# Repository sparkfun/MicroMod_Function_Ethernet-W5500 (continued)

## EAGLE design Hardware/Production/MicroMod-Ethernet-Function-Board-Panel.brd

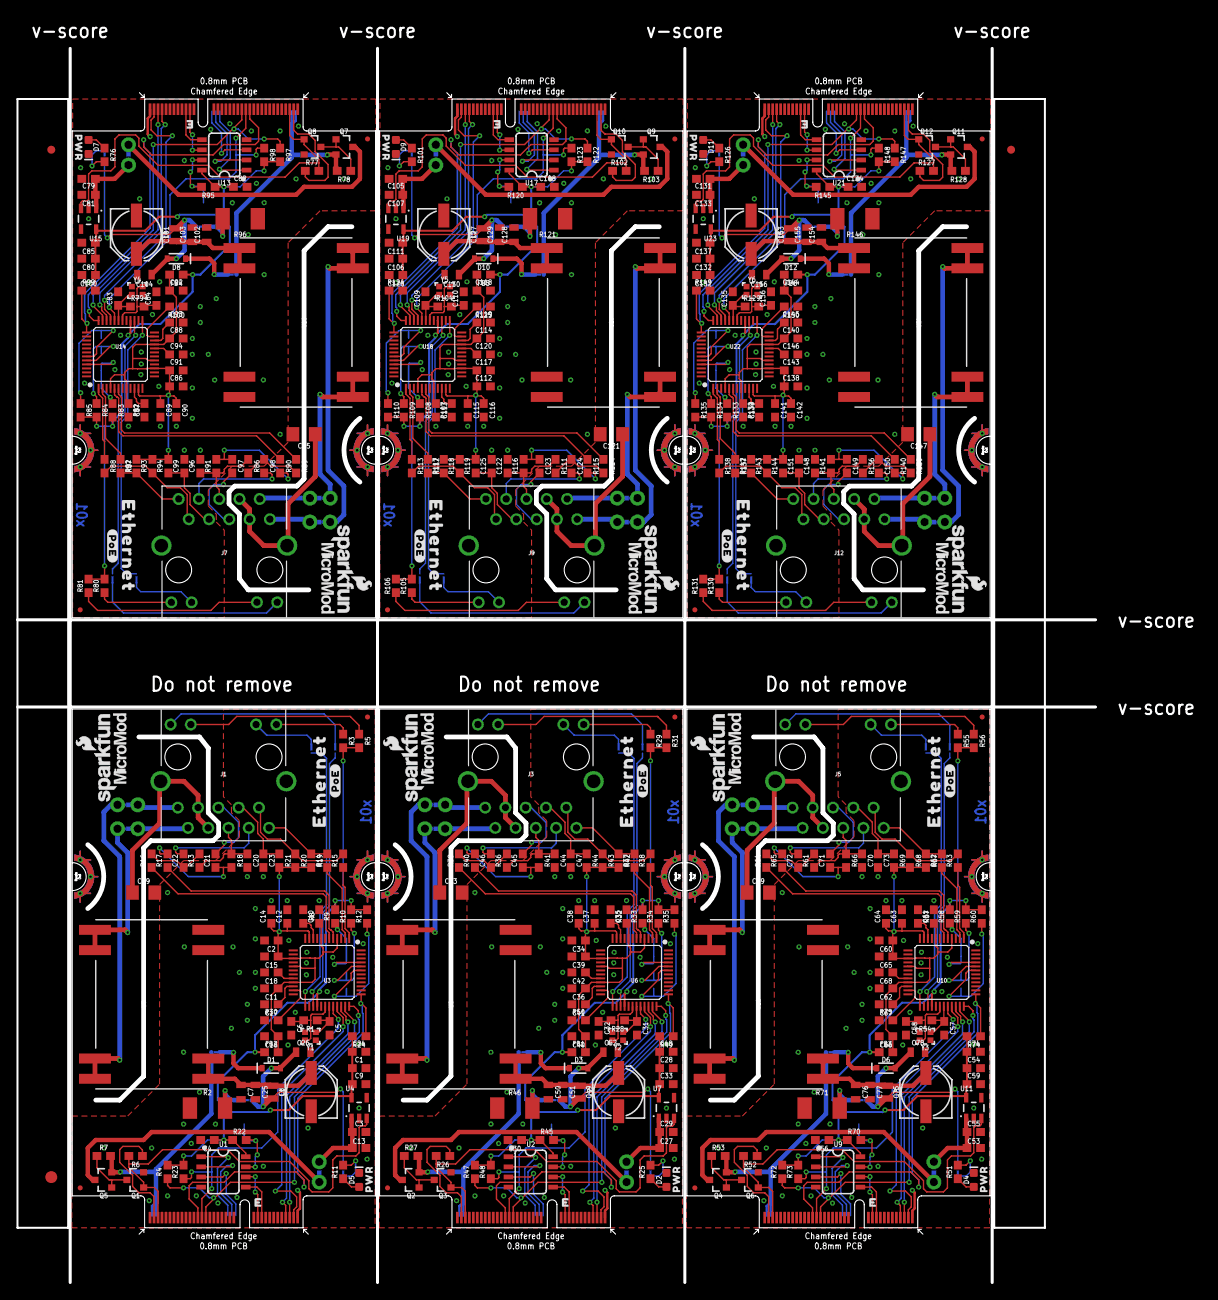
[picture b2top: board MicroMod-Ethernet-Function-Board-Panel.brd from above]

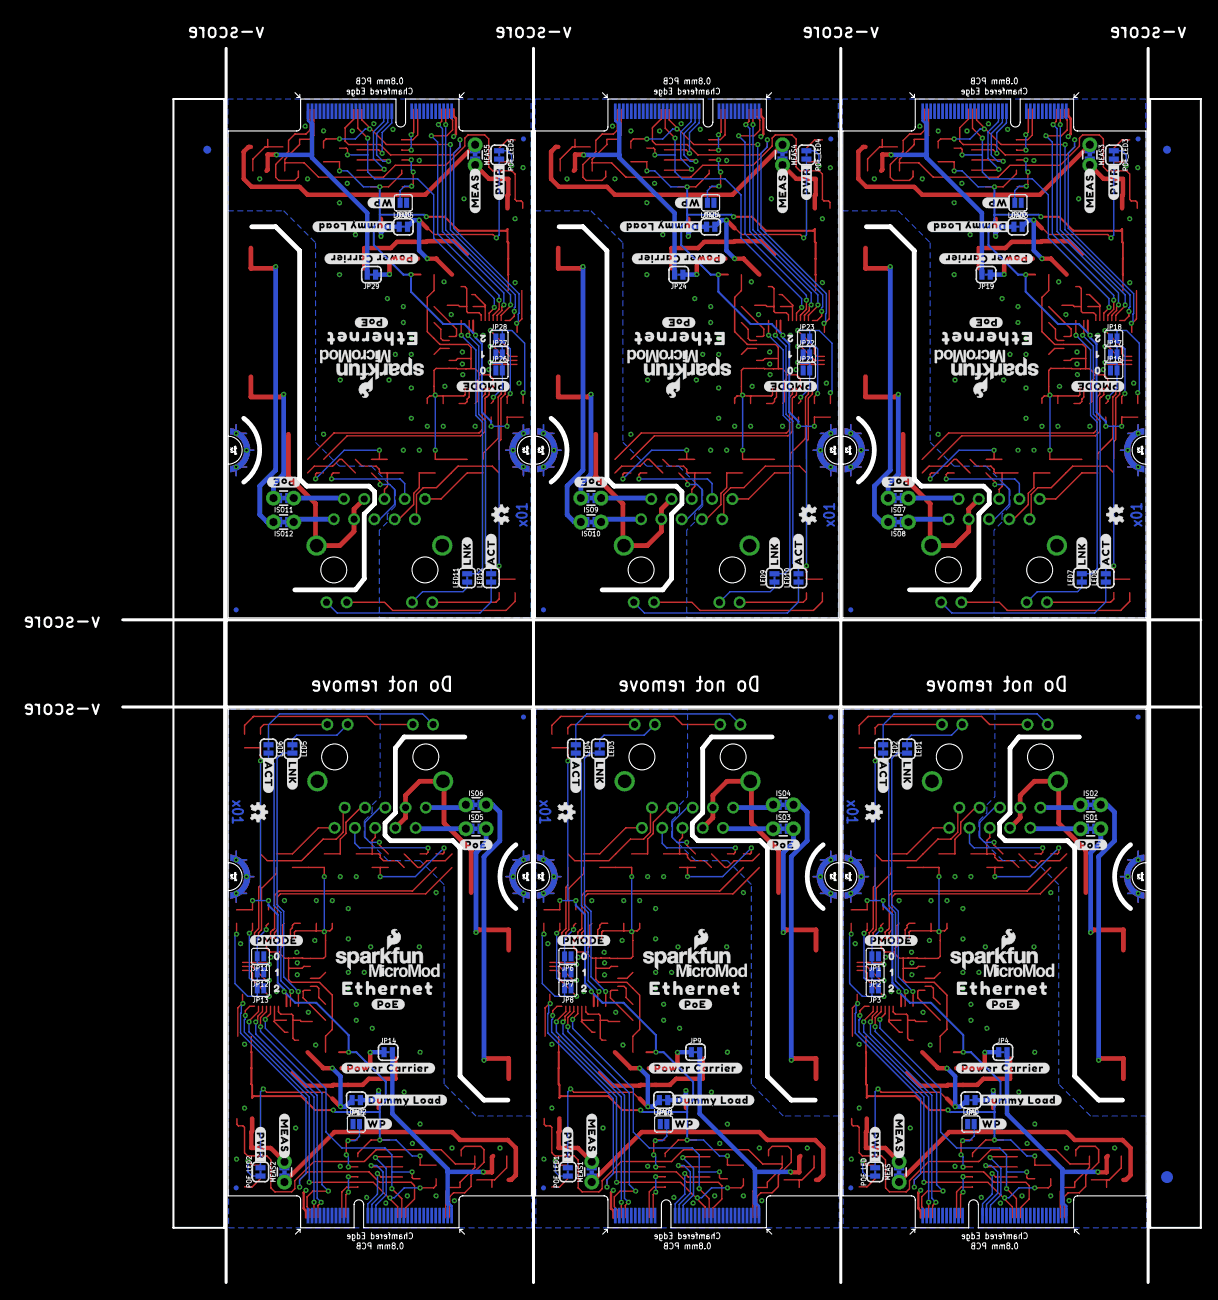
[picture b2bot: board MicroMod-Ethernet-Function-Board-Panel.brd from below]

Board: 2 copper layers, 135.1 x 154.6 mm, 618 parts (189 on the bottom side), 354 nets.

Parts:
C1, C2, C3, C4, C10, C11, C12, C14, C15, C28, C29, C30, C34, C35, C36, C37, C38, C39, C54, C55, C56, C60, C61, C62, C63, C64, C65, C80, C81, C82, C86, C87, C88, C89, C90, C91, C106, C107, C108, C112, C113, C114, C115, C116, C117, C132, C133, C134, C138, C139, C140, C141, C142, C143: 0.1uF; 0603
C5, C6, C31, C32, C57, C58, C83, C84, C109, C110, C135, C136: 10pF; 0603
C7, C25, C26, C50, C51, C52, C76, C77, C78, C102, C103, C104, C128, C129, C130, C154, C155, C156: 10uF; 0805
C8, C49, C75, C101, C127, C153: 100uF; PANASONIC_D
C9, C16, C33, C40, C59, C66, C85, C92, C111, C118, C137, C144: 10uF; 0603
C13, C24, C27, C48, C53, C74, C79, C100, C105, C126, C131, C152: 1.0uF; 0603
C17, C20, C41, C44, C67, C70, C93, C96, C119, C122, C145, C148: 10nF; 0603
C18, C42, C68, C94, C120, C146: 4.7uF; 0603
C19, C43, C69, C95, C121, C147: 1nF; 1206
C21, C22, C45, C46, C71, C72, C97, C98, C123, C124, C149, C150: 6.8nF; 0603
C23, C47, C73, C99, C125, C151: 22nF; 0603
D1, D3, D6, D8, D10, D12: 3A/10V/280mV; SOD-323
D2, D4, D5, D7, D9, D11: RED; LED-0603
E$1, E$2, E$3, E$4: FIDUCIAL-1X2
E$5, E$6: FIDUCIAL-1.5X3
FB1, FB2, FB3, FB4, FB5, FB6: 470Ω; 0603
FD1, FD2, FD3, FD4, FD5, FD6, FD7, FD8, FD9, FD10, FD11, FD12, FD13, FD14, FD15, FD16, FD17, FD18, FD19, FD20, FD21, FD22, FD23, FD24: FIDUCIALUFIDUCIAL; FIDUCIAL-MICRO
ISO1, ISO2, ISO3, ISO4, ISO5, ISO6, ISO7, ISO8, ISO9, ISO10, ISO11, ISO12: COMBO-JUMPER_2_NC_TRACE
J1, J3, J5, J7, J9, J12: MAGJACK_SYM; MAGJACK-STR_LED
J2, J4, J6, J8, J10, J11: MICROMOD_STANDARD; M.2-CARD-E-22_FUNCTION_STANDARD
JP1, JP2, JP3, JP6, JP7, JP8, JP11, JP12, JP13, JP16, JP17, JP18, JP21, JP22, JP23, JP26, JP27, JP28: SMT-JUMPER_2_NO_SILK
JP4, JP9, JP14, JP19, JP24, JP29: PoE System; SMT-JUMPER_2_NC_TRACE_SILK
JP5, JP10, JP15, JP20, JP25, JP30: JUMPER-SMT_2_NO_SILK; SMT-JUMPER_2_NO_SILK
L1, L2, L3, L4, L5, L6: 2.2uH; 0805-WIDE
LED1, LED2, LED3, LED4, LED5, LED6, LED7, LED8, LED9, LED10, LED11, LED12: JUMPER-SMT_2_NC_TRACE_SILK; SMT-JUMPER_2_NC_TRACE_SILK
LOAD, LOAD1, LOAD2, LOAD3, LOAD4, LOAD5: SMT-JUMPER_2_NC_TRACE_SILK
LOGO1, LOGO2, LOGO4, LOGO6, LOGO7, LOGO9, LOGO10, LOGO12, LOGO13, LOGO15, LOGO16, LOGO18: SFE_LOGO_NAME_FLAME.1_INCH; SFE_LOGO_NAME_FLAME_.1
LOGO3, LOGO5, LOGO8, LOGO11, LOGO14, LOGO17: OSHW-LOGOMINI; OSHW-LOGO-MINI
MEAS, MEAS1, MEAS2, MEAS3, MEAS4, MEAS5: COMBO-JUMPER_2_NC_TRACE
POE_LED, POE_LED1, POE_LED2, POE_LED3, POE_LED4, POE_LED5: SMT-JUMPER_2_NC_TRACE_SILK
Q1, Q3, Q6, Q8, Q10, Q12: 220mA/50V/3.5Ω; SOT23-3
Q2, Q4, Q5, Q7, Q9, Q11: 20V/4.2A/52mΩ/1.4W; SOT23-3
R1, R28, R54, R79, R104, R129: 1M; 0603
R2, R46, R71, R96, R121, R146: 510; 2010
R3, R5, R11, R25, R29, R31, R51, R55, R56, R76, R80, R81, R101, R105, R106, R126, R130, R131: 1k; 0603
R4, R6, R7, R9, R10, R12, R22, R23, R24, R26, R27, R30, R33, R34, R35, R45, R47, R48, R49, R50, R52, R53, R58, R59, R60, R70, R72, R73, R74, R75, R77, R78, R83, R84, R85, R95, R97, R98, R99, R100, R102, R103, R108, R109, R110, R120, R122, R123, R124, R125, R127, R128, R133, R134, R135, R145, R147, R148, R149, R150: 10k; 0603
R8, R32, R57, R82, R107, R132: 12.4k; 0603
R13, R18, R19, R20, R36, R41, R42, R43, R61, R66, R67, R68, R86, R91, R92, R93, R111, R116, R117, R118, R136, R141, R142, R143: 49.9; 0603
R14, R15, R16, R17, R37, R38, R39, R40, R62, R63, R64, R65, R87, R88, R89, R90, R112, R113, R114, R115, R137, R138, R139, R140: 33; 0603
R21, R44, R69, R94, R119, R144: 10; 0603
U1, U2, U9, U13, U17, U21: EEPROM; SO08
U3, U6, U10, U14, U18, U22: W5500; LQFP-48
U4, U7, U11, U15, U19, U23: 3.3V; SOT23-5
U5, U8, U12, U16, U20, U24: POE_PSU-DP990X; DP990X
U$1, U$17, U$26, U$29, U$47, U$49, U$67, U$69, U$86, U$88, U$105, U$107: ETHERNET0
U$2, U$18, U$19, U$27, U$30, U$36, U$48, U$50, U$56, U$68, U$70, U$76, U$87, U$89, U$95, U$106, U$108, U$114: #POE#0
U$3, U$31, U$51, U$71, U$90, U$109: #POWER_CARRIER#0
U$4, U$10, U$37, U$38, U$39, U$57, U$58, U$63, U$77, U$78, U$96, U$97: MICROMOD_LOGO_.35
U$5, U$32, U$52, U$72, U$91, U$110: #DUMMY_LOAD#0
U$6, U$33, U$53, U$73, U$92, U$111: #WP#0
U$7, U$20, U$41, U$60, U$80, U$99: PWR0
U$8, U$34, U$54, U$74, U$93, U$112: #ACT#0
U$9, U$21, U$42, U$61, U$81, U$100: #PWR#0
U$11, U$28, U$40, U$59, U$79, U$98: #MEAS#3
U$12, U$35, U$55, U$75, U$94, U$113: #LNK#1
U$13, U$22, U$43, U$62, U$82, U$101: #PMODE#0
U$14, U$23, U$44, U$64, U$83, U$102: 01
U$15, U$24, U$45, U$65, U$84, U$103: 12
U$16, U$25, U$46, U$66, U$85, U$104: 23
Y1, Y2, Y3, Y4, Y5, Y6: 25MHz; CRYSTAL-SMD-2.0X1.6MM

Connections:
3.3V: C1.1, C4.1, C9.1, C24.1, FB2.1, R3.2, R4.2, R5.2, R9.2, R10.2, R12.2, R22.1, R23.2, R24.2, U1.8, U3.28, U4.5
3.3V1: C28.1, C30.1, C33.1, C48.1, FB1.1, R29.2, R31.2, R33.2, R34.2, R35.2, R45.1, R47.2, R48.2, R49.2, U2.8, U6.28, U7.5
3.3V2: C54.1, C56.1, C59.1, C74.1, FB3.1, R55.2, R56.2, R58.2, R59.2, R60.2, R70.1, R72.2, R73.2, R74.2, U9.8, U10.28, U11.5
3.3V3: C80.1, C82.1, C85.1, C100.1, FB4.1, R80.2, R81.2, R83.2, R84.2, R85.2, R95.1, R97.2, R98.2, R99.2, U13.8, U14.28, U15.5
3.3V4: C106.1, C108.1, C111.1, C126.1, FB5.1, R105.2, R106.2, R108.2, R109.2, R110.2, R120.1, R122.2, R123.2, R124.2, U17.8, U18.28, U19.5
3.3V5: C132.1, C134.1, C137.1, C152.1, FB6.1, R130.2, R131.2, R133.2, R134.2, R135.2, R145.1, R147.2, R148.2, R149.2, U21.8, U22.28, U23.5
3.3V_IN: J11.73, R6.1
3.3V_IN1: J2.73, R26.1
3.3V_IN2: J4.73, R52.1
3.3V_IN3: J6.73, R77.1
3.3V_IN4: J8.73, R102.1
3.3V_IN5: J10.73, R127.1
5V: C3.1, C13.1, MEAS.2, MEAS.4, U4.1
5V1: C27.1, C29.1, MEAS1.2, MEAS1.4, U7.1
5V2: C53.1, C55.1, MEAS2.2, MEAS2.4, U11.1
5V3: C79.1, C81.1, MEAS3.2, MEAS3.4, U15.1
5V4: C105.1, C107.1, MEAS4.2, MEAS4.4, U19.1
5V5: C131.1, C133.1, MEAS5.2, MEAS5.4, U23.1
5V_FILTER: C26.1, D1.A, L1.2, LOAD.2, POE_LED.2
5V_FILTER1: C52.1, D3.A, L2.2, LOAD1.2, POE_LED1.2
5V_FILTER2: C78.1, D6.A, L3.2, LOAD2.2, POE_LED2.2
5V_FILTER3: C104.1, D8.A, L4.2, LOAD3.2, POE_LED3.2
5V_FILTER4: C130.1, D10.A, L5.2, LOAD4.2, POE_LED4.2
5V_FILTER5: C156.1, D12.A, L6.2, LOAD5.2, POE_LED5.2
5V_RAW: C7.1, C8.+, C25.1, L1.1, U5.1, U5.2
5V_RAW1: C49.+, C50.1, C51.1, L2.1, U8.1, U8.2
5V_RAW2: C75.+, C76.1, C77.1, L3.1, U12.1, U12.2
5V_RAW3: C101.+, C102.1, C103.1, L4.1, U16.1, U16.2
5V_RAW4: C127.+, C128.1, C129.1, L5.1, U20.1, U20.2
5V_RAW5: C153.+, C154.1, C155.1, L6.1, U24.1, U24.2
A0: J11.36, U1.1
A1: J11.34, U1.2
A2: J11.32, U1.3
A3: J2.36, U2.1
A4: J2.32, U2.3
A5: J2.34, U2.2
A6: J4.36, U9.1
A7: J4.32, U9.3
A8: J4.34, U9.2
A9: J6.36, U13.1
A10: J6.32, U13.3
A11: J6.34, U13.2
A12: J8.36, U17.1
A13: J8.32, U17.3
A14: J8.34, U17.2
A15: J10.36, U21.1
A16: J10.32, U21.3
A17: J10.34, U21.2
ACT_LED: LED2.2, U3.27
ACT_LED1: LED4.2, U6.27
ACT_LED2: LED6.2, U10.27
ACT_LED3: LED8.2, U14.27
ACT_LED4: LED10.2, U18.27
ACT_LED5: LED12.2, U22.27
ETH_!CS!: J11.49, R23.1, U3.32
ETH_!CS!1: J2.49, R48.1, U6.32
ETH_!CS!2: J4.49, R73.1, U10.32
ETH_!CS!3: J6.49, R98.1, U14.32
ETH_!CS!4: J8.49, R123.1, U18.32
ETH_!CS!5: J10.49, R148.1, U22.32
ETH_!INT!: J11.47, R4.1, U3.36
ETH_!INT!1: J2.47, R47.1, U6.36
ETH_!INT!2: J4.47, R72.1, U10.36
ETH_!INT!3: J6.47, R97.1, U14.36
ETH_!INT!4: J8.47, R122.1, U18.36
ETH_!INT!5: J10.47, R147.1, U22.36
ETH_!RST!: J11.51, R24.1, U3.37
ETH_!RST!1: J2.51, R49.1, U6.37
ETH_!RST!2: J4.51, R74.1, U10.37
ETH_!RST!3: J6.51, R99.1, U14.37
ETH_!RST!4: J8.51, R124.1, U18.37
ETH_!RST!5: J10.51, R149.1, U22.37
GND: C1.2, C2.2, C3.2, C4.2, C5.2, C6.2, C7.2, C8.-, C9.2, C10.2, C11.2, C12.2, C13.2, C14.2, C15.2, C16.2, C17.2, C18.2, C19.2, C20.2, C23.2, C24.2, C25.2, C26.2, D5.C, J11.1, J11.33, J11.39, J11.45, J11.75, J11.GND1, J11.GND2, J11.GND3, J11.GND4, J11.GND5, J11.GND6, JP1.1, JP2.1, JP3.1, JP5.1, Q1.2, R2.1, R8.1, R30.1, U1.4, U3.3, U3.9, U3.14, U3.16, U3.19, U3.29, U3.48, U4.2, U5.3
GND1: C27.2, C28.2, C29.2, C30.2, C31.2, C32.2, C33.2, C34.2, C35.2, C36.2, C37.2, C38.2, C39.2, C40.2, C41.2, C42.2, C43.2, C44.2, C47.2, C48.2, C49.-, C50.2, C51.2, C52.2, D2.C, J2.1, J2.33, J2.39, J2.45, J2.75, J2.GND1, J2.GND2, J2.GND3, J2.GND4, J2.GND5, J2.GND6, JP6.1, JP7.1, JP8.1, JP10.1, Q3.2, R32.1, R46.1, R50.1, U2.4, U6.3, U6.9, U6.14, U6.16, U6.19, U6.29, U6.48, U7.2, U8.3
GND2: C53.2, C54.2, C55.2, C56.2, C57.2, C58.2, C59.2, C60.2, C61.2, C62.2, C63.2, C64.2, C65.2, C66.2, C67.2, C68.2, C69.2, C70.2, C73.2, C74.2, C75.-, C76.2, C77.2, C78.2, D4.C, J4.1, J4.33, J4.39, J4.45, J4.75, J4.GND1, J4.GND2, J4.GND3, J4.GND4, J4.GND5, J4.GND6, JP11.1, JP12.1, JP13.1, JP15.1, Q6.2, R57.1, R71.1, R75.1, U9.4, U10.3, U10.9, U10.14, U10.16, U10.19, U10.29, U10.48, U11.2, U12.3
GND3: C79.2, C80.2, C81.2, C82.2, C83.2, C84.2, C85.2, C86.2, C87.2, C88.2, C89.2, C90.2, C91.2, C92.2, C93.2, C94.2, C95.2, C96.2, C99.2, C100.2, C101.-, C102.2, C103.2, C104.2, D7.C, J6.1, J6.33, J6.39, J6.45, J6.75, J6.GND1, J6.GND2, J6.GND3, J6.GND4, J6.GND5, J6.GND6, JP16.1, JP17.1, JP18.1, JP20.1, Q8.2, R82.1, R96.1, R100.1, U13.4, U14.3, U14.9, U14.14, U14.16, U14.19, U14.29, U14.48, U15.2, U16.3
GND4: C105.2, C106.2, C107.2, C108.2, C109.2, C110.2, C111.2, C112.2, C113.2, C114.2, C115.2, C116.2, C117.2, C118.2, C119.2, C120.2, C121.2, C122.2, C125.2, C126.2, C127.-, C128.2, C129.2, C130.2, D9.C, J8.1, J8.33, J8.39, J8.45, J8.75, J8.GND1, J8.GND2, J8.GND3, J8.GND4, J8.GND5, J8.GND6, JP21.1, JP22.1, JP23.1, JP25.1, Q10.2, R107.1, R121.1, R125.1, U17.4, U18.3, U18.9, U18.14, U18.16, U18.19, U18.29, U18.48, U19.2, U20.3
GND5: C131.2, C132.2, C133.2, C134.2, C135.2, C136.2, C137.2, C138.2, C139.2, C140.2, C141.2, C142.2, C143.2, C144.2, C145.2, C146.2, C147.2, C148.2, C151.2, C152.2, C153.-, C154.2, C155.2, C156.2, D11.C, J10.1, J10.33, J10.39, J10.45, J10.75, J10.GND1, J10.GND2, J10.GND3, J10.GND4, J10.GND5, J10.GND6, JP26.1, JP27.1, JP28.1, JP30.1, Q12.2, R132.1, R146.1, R150.1, U21.4, U22.3, U22.9, U22.14, U22.16, U22.19, U22.29, U22.48, U23.2, U24.3
GND-ISO: C19.1, J1.7, J1.8, J1.S1, J1.S2
GND-ISO1: C43.1, J3.7, J3.8, J3.S1, J3.S2
GND-ISO2: C69.1, J5.7, J5.8, J5.S1, J5.S2
GND-ISO3: C95.1, J7.7, J7.8, J7.S1, J7.S2
GND-ISO4: C121.1, J9.7, J9.8, J9.S1, J9.S2
GND-ISO5: C147.1, J12.7, J12.8, J12.S1, J12.S2
I2C_SCL: J11.21, U1.6
I2C_SCL1: J2.21, U2.6
I2C_SCL2: J4.21, U9.6
I2C_SCL3: J6.21, U13.6
I2C_SCL4: J8.21, U17.6
I2C_SCL5: J10.21, U21.6
I2C_SDA: J11.19, U1.5
I2C_SDA1: J2.19, U2.5
I2C_SDA2: J4.19, U9.5
I2C_SDA3: J6.19, U13.5
I2C_SDA4: J8.19, U17.5
I2C_SDA5: J10.19, U21.5
LINK_LED: LED1.2, U3.25
LINK_LED1: LED3.2, U6.25
LINK_LED2: LED5.2, U10.25
LINK_LED3: LED7.2, U14.25
LINK_LED4: LED9.2, U18.25
LINK_LED5: LED11.2, U22.25
unnamed: C5.1, R1.1, U3.31, Y1.1
unnamed: C6.1, R1.2, U3.30, Y1.3
unnamed: J1.14, LED2.1
unnamed: J1.12, LED1.1
unnamed: D5.A, R11.1
unnamed: POE_LED.1, R11.2
unnamed: D1.C, JP4.1
unnamed: J1.13, R5.1
unnamed: LOAD.1, R2.2
unnamed: J1.11, R3.1
unnamed: Q1.3, Q5.1, R7.1
unnamed: JP5.2, R22.2, U1.7
unnamed: R8.2, U3.10
unnamed: ISO1.2, ISO1.4, U5.5, U5.6
unnamed: C17.1, U3.22
unnamed: C18.1, U3.20
unnamed: R30.2, U3.23
unnamed: ISO2.2, ISO2.4, U5.7, U5.8
unnamed: POE_LED1.1, R25.2
unnamed: D2.A, R25.1
unnamed: Q2.1, Q3.3, R27.1
unnamed: C31.1, R28.1, U6.31, Y2.1
unnamed: C32.1, R28.2, U6.30, Y2.3
unnamed: J3.13, R31.1
unnamed: J3.11, R29.1
unnamed: R32.2, U6.10
unnamed: C41.1, U6.22
unnamed: C42.1, U6.20
unnamed: D3.C, JP9.1
unnamed: LOAD1.1, R46.2
unnamed: ISO3.2, ISO3.4, U8.5, U8.6
unnamed: ISO4.2, ISO4.4, U8.7, U8.8
unnamed: JP10.2, R45.2, U2.7
unnamed: J3.12, LED3.1
unnamed: J3.14, LED4.1
unnamed: R50.2, U6.23
unnamed: POE_LED2.1, R51.2
unnamed: D4.A, R51.1
unnamed: Q4.1, Q6.3, R53.1
unnamed: C57.1, R54.1, U10.31, Y3.1
unnamed: C58.1, R54.2, U10.30, Y3.3
unnamed: J5.13, R56.1
unnamed: J5.11, R55.1
unnamed: R57.2, U10.10
unnamed: C67.1, U10.22
unnamed: C68.1, U10.20
unnamed: D6.C, JP14.1
unnamed: LOAD2.1, R71.2
unnamed: ISO5.2, ISO5.4, U12.5, U12.6
unnamed: ISO6.2, ISO6.4, U12.7, U12.8
unnamed: JP15.2, R70.2, U9.7
unnamed: J5.12, LED5.1
unnamed: J5.14, LED6.1
unnamed: R75.2, U10.23
unnamed: POE_LED3.1, R76.2
unnamed: D7.A, R76.1
unnamed: Q7.1, Q8.3, R78.1
unnamed: C83.1, R79.1, U14.31, Y4.1
unnamed: C84.1, R79.2, U14.30, Y4.3
unnamed: J7.13, R81.1
unnamed: J7.11, R80.1
unnamed: R82.2, U14.10
unnamed: C93.1, U14.22
unnamed: C94.1, U14.20
unnamed: D8.C, JP19.1
unnamed: LOAD3.1, R96.2
unnamed: ISO7.2, ISO7.4, U16.5, U16.6
unnamed: ISO8.2, ISO8.4, U16.7, U16.8
unnamed: JP20.2, R95.2, U13.7
unnamed: J7.12, LED7.1
unnamed: J7.14, LED8.1
unnamed: R100.2, U14.23
unnamed: POE_LED4.1, R101.2
unnamed: D9.A, R101.1
unnamed: Q9.1, Q10.3, R103.1
unnamed: C109.1, R104.1, U18.31, Y5.1
unnamed: C110.1, R104.2, U18.30, Y5.3
unnamed: J9.13, R106.1
unnamed: J9.11, R105.1
unnamed: R107.2, U18.10
unnamed: C119.1, U18.22
unnamed: C120.1, U18.20
unnamed: D10.C, JP24.1
unnamed: LOAD4.1, R121.2
unnamed: ISO9.2, ISO9.4, U20.5, U20.6
unnamed: ISO10.2, ISO10.4, U20.7, U20.8
unnamed: JP25.2, R120.2, U17.7
unnamed: J9.12, LED9.1
unnamed: J9.14, LED10.1
unnamed: R125.2, U18.23
unnamed: POE_LED5.1, R126.2
unnamed: D11.A, R126.1
unnamed: Q11.1, Q12.3, R128.1
unnamed: C135.1, R129.1, U22.31, Y6.1
unnamed: C136.1, R129.2, U22.30, Y6.3
unnamed: J12.13, R131.1
unnamed: J12.11, R130.1
unnamed: R132.2, U22.10
unnamed: C145.1, U22.22
unnamed: C146.1, U22.20
unnamed: D12.C, JP29.1
unnamed: LOAD5.1, R146.2
unnamed: ISO11.2, ISO11.4, U24.5, U24.6
unnamed: ISO12.2, ISO12.4, U24.7, U24.8
unnamed: JP30.2, R145.2, U21.7
unnamed: J12.12, LED11.1
unnamed: J12.14, LED12.1
unnamed: R150.2, U22.23
PMODE0: JP1.2, R9.1, U3.45
PMODE1: JP2.2, R10.1, U3.44
PMODE2: JP3.2, R12.1, U3.43
PMODE3: JP6.2, R33.1, U6.45
PMODE4: JP7.2, R34.1, U6.44
PMODE5: JP8.2, R35.1, U6.43
PMODE6: JP11.2, R58.1, U10.45
PMODE7: JP12.2, R59.1, U10.44
PMODE8: JP13.2, R60.1, U10.43
PMODE9: JP16.2, R83.1, U14.45
PMODE10: JP17.2, R84.1, U14.44
PMODE11: JP18.2, R85.1, U14.43
PMODE12: JP21.2, R108.1, U18.45
PMODE13: JP22.2, R109.1, U18.44
PMODE14: JP23.2, R110.1, U18.43
PMODE15: JP26.2, R133.1, U22.45
PMODE16: JP27.2, R134.1, U22.44
PMODE17: JP28.2, R135.1, U22.43
PW+: ISO1.1, ISO1.3, J1.9
PW+1: ISO3.1, ISO3.3, J3.9
PW+2: ISO5.1, ISO5.3, J5.9
PW+3: ISO7.1, ISO7.3, J7.9
PW+4: ISO9.1, ISO9.3, J9.9
PW+5: ISO11.1, ISO11.3, J12.9
PW-: ISO2.1, ISO2.3, J1.10
PW-1: ISO4.1, ISO4.3, J3.10
PW-2: ISO6.1, ISO6.3, J5.10
PW-3: ISO8.1, ISO8.3, J7.10
PW-4: ISO10.1, ISO10.3, J9.10
PW-5: ISO12.1, ISO12.3, J12.10
PWR_EN: J11.71, Q1.1, R6.2, U4.3
PWR_EN1: J2.71, Q3.1, R26.2, U7.3
PWR_EN2: J4.71, Q6.1, R52.2, U11.3
PWR_EN3: J6.71, Q8.1, R77.2, U15.3
PWR_EN4: J8.71, Q10.1, R102.2, U19.3
PWR_EN5: J10.71, Q12.1, R127.2, U23.3
RCT: C20.1, J1.5, R13.1, R18.1
RCT1: C44.1, J3.5, R36.1, R41.1
RCT2: C70.1, J5.5, R61.1, R66.1
RCT3: C96.1, J7.5, R86.1, R91.1
RCT4: C122.1, J9.5, R111.1, R116.1
RCT5: C148.1, J12.5, R136.1, R141.1
RD+: C22.2, J1.3
RD+1: C46.2, J3.3
RD+2: C72.2, J5.3
RD+3: C98.2, J7.3
RD+4: C124.2, J9.3
RD+5: C150.2, J12.3
RD-: C21.2, J1.6
RD-1: C45.2, J3.6
RD-2: C71.2, J5.6
RD-3: C97.2, J7.6
RD-4: C123.2, J9.6
RD-5: C149.2, J12.6
RXN: R17.1, U3.5
RXN1: C21.1, R17.2, R18.2
RXN2: R40.1, U6.5
RXN3: C45.1, R40.2, R41.2
RXN4: R65.1, U10.5
RXN5: C71.1, R65.2, R66.2
RXN6: R90.1, U14.5
RXN7: C97.1, R90.2, R91.2
RXN8: R115.1, U18.5
RXN9: C123.1, R115.2, R116.2
RXN10: R140.1, U22.5
RXN11: C149.1, R140.2, R141.2
RXP: R16.1, U3.6
RXP1: C22.1, R13.2, R16.2
RXP2: R39.1, U6.6
RXP3: C46.1, R36.2, R39.2
RXP4: R64.1, U10.6
RXP5: C72.1, R61.2, R64.2
RXP6: R89.1, U14.6
RXP7: C98.1, R86.2, R89.2
RXP8: R114.1, U18.6
RXP9: C124.1, R111.2, R114.2
RXP10: R139.1, U22.6
RXP11: C150.1, R136.2, R139.2
SPI_CIPO: J11.7, U3.34
SPI_CIPO1: J2.7, U6.34
SPI_CIPO2: J4.7, U10.34
SPI_CIPO3: J6.7, U14.34
SPI_CIPO4: J8.7, U18.34
SPI_CIPO5: J10.7, U22.34
SPI_COPI: J11.5, U3.35
SPI_COPI1: J2.5, U6.35
SPI_COPI2: J4.5, U10.35
SPI_COPI3: J6.5, U14.35
SPI_COPI4: J8.5, U18.35
SPI_COPI5: J10.5, U22.35
SPI_SCK: J11.3, U3.33
SPI_SCK1: J2.3, U6.33
SPI_SCK2: J4.3, U10.33
SPI_SCK3: J6.3, U14.33
SPI_SCK4: J8.3, U18.33
SPI_SCK5: J10.3, U22.33
TCT: C23.1, J1.4, R21.1
TCT1: C47.1, J3.4, R44.1
TCT2: C73.1, J5.4, R69.1
TCT3: C99.1, J7.4, R94.1
TCT4: C125.1, J9.4, R119.1
TCT5: C151.1, J12.4, R144.1
TD+: J1.1, R14.2, R19.1
TD+1: J3.1, R37.2, R42.1
TD+2: J5.1, R62.2, R67.1
TD+3: J7.1, R87.2, R92.1
TD+4: J9.1, R112.2, R117.1
TD+5: J12.1, R137.2, R142.1
TD-: J1.2, R15.2, R20.1
TD-1: J3.2, R38.2, R43.1
TD-2: J5.2, R63.2, R68.1
TD-3: J7.2, R88.2, R93.1
TD-4: J9.2, R113.2, R118.1
TD-5: J12.2, R138.2, R143.1
TXN: R15.1, U3.1
TXN1: R38.1, U6.1
TXN2: R63.1, U10.1
TXN3: R88.1, U14.1
TXN4: R113.1, U18.1
TXN5: R138.1, U22.1
TXP: R14.1, U3.2
TXP1: R37.1, U6.2
TXP2: R62.1, U10.2
TXP3: R87.1, U14.2
TXP4: R112.1, U18.2
TXP5: R137.1, U22.2
VCC: MEAS.1, MEAS.3, Q5.3
VCC1: MEAS1.1, MEAS1.3, Q2.3
VCC2: MEAS2.1, MEAS2.3, Q4.3
VCC3: MEAS3.1, MEAS3.3, Q7.3
VCC4: MEAS4.1, MEAS4.3, Q9.3
VCC5: MEAS5.1, MEAS5.3, Q11.3
VCCA: C2.1, C10.1, C11.1, C12.1, C14.1, C15.1, C16.1, FB2.2, R19.2, R20.2, R21.2, U3.4, U3.8, U3.11, U3.15, U3.17, U3.21
VCCA1: C34.1, C35.1, C36.1, C37.1, C38.1, C39.1, C40.1, FB1.2, R42.2, R43.2, R44.2, U6.4, U6.8, U6.11, U6.15, U6.17, U6.21
VCCA2: C60.1, C61.1, C62.1, C63.1, C64.1, C65.1, C66.1, FB3.2, R67.2, R68.2, R69.2, U10.4, U10.8, U10.11, U10.15, U10.17, U10.21
VCCA3: C86.1, C87.1, C88.1, C89.1, C90.1, C91.1, C92.1, FB4.2, R92.2, R93.2, R94.2, U14.4, U14.8, U14.11, U14.15, U14.17, U14.21
VCCA4: C112.1, C113.1, C114.1, C115.1, C116.1, C117.1, C118.1, FB5.2, R117.2, R118.2, R119.2, U18.4, U18.8, U18.11, U18.15, U18.17, U18.21
VCCA5: C138.1, C139.1, C140.1, C141.1, C142.1, C143.1, C144.1, FB6.2, R142.2, R143.2, R144.2, U22.4, U22.8, U22.11, U22.15, U22.17, U22.21
VCC_IN: J11.72, J11.74, JP4.2, Q5.2, R7.2
VCC_IN1: J2.72, J2.74, JP9.2, Q2.2, R27.2
VCC_IN2: J4.72, J4.74, JP14.2, Q4.2, R53.2
VCC_IN3: J6.72, J6.74, JP19.2, Q7.2, R78.2
VCC_IN4: J8.72, J8.74, JP24.2, Q9.2, R103.2
VCC_IN5: J10.72, J10.74, JP29.2, Q11.2, R128.2

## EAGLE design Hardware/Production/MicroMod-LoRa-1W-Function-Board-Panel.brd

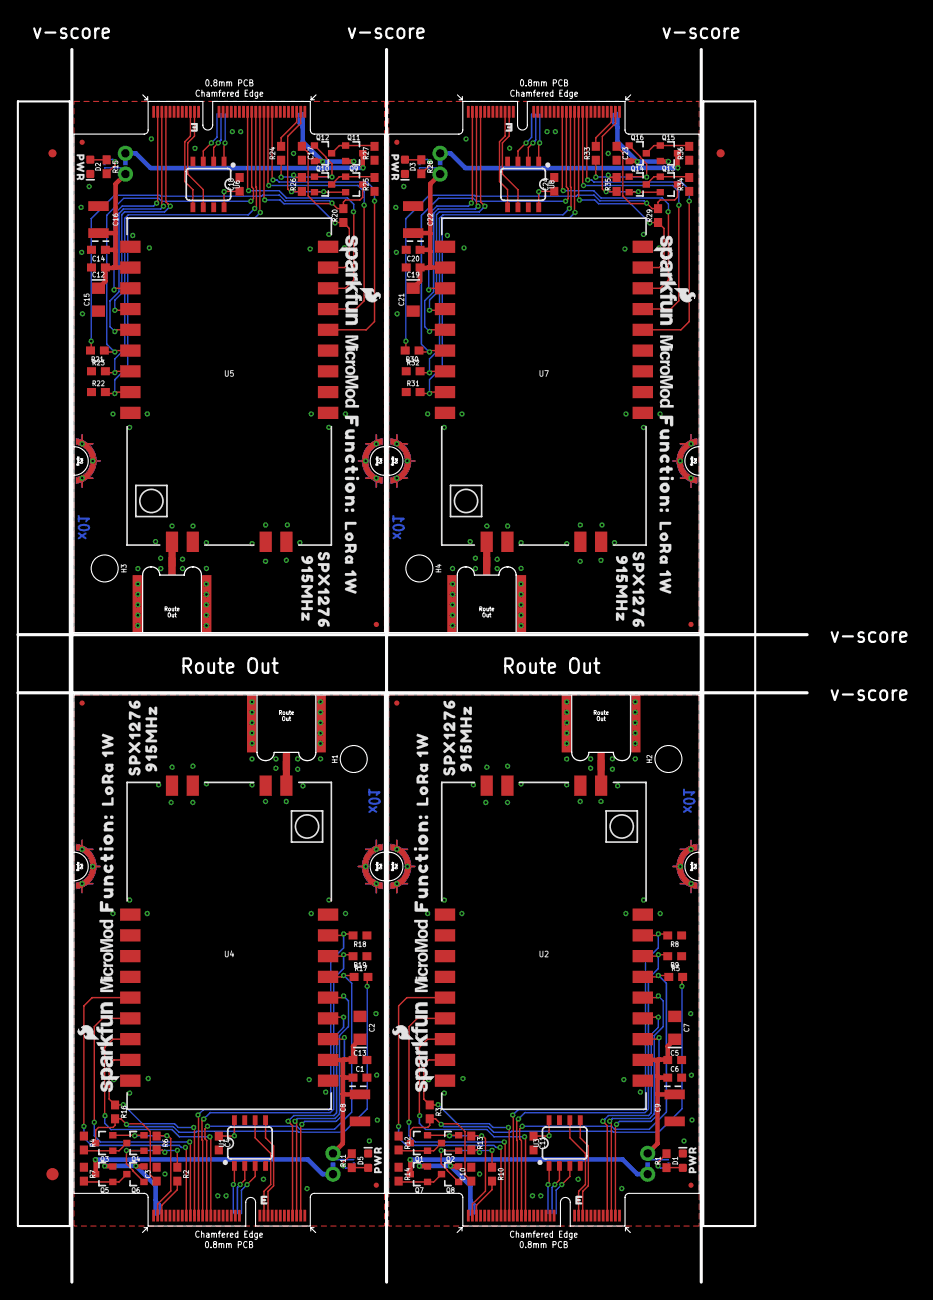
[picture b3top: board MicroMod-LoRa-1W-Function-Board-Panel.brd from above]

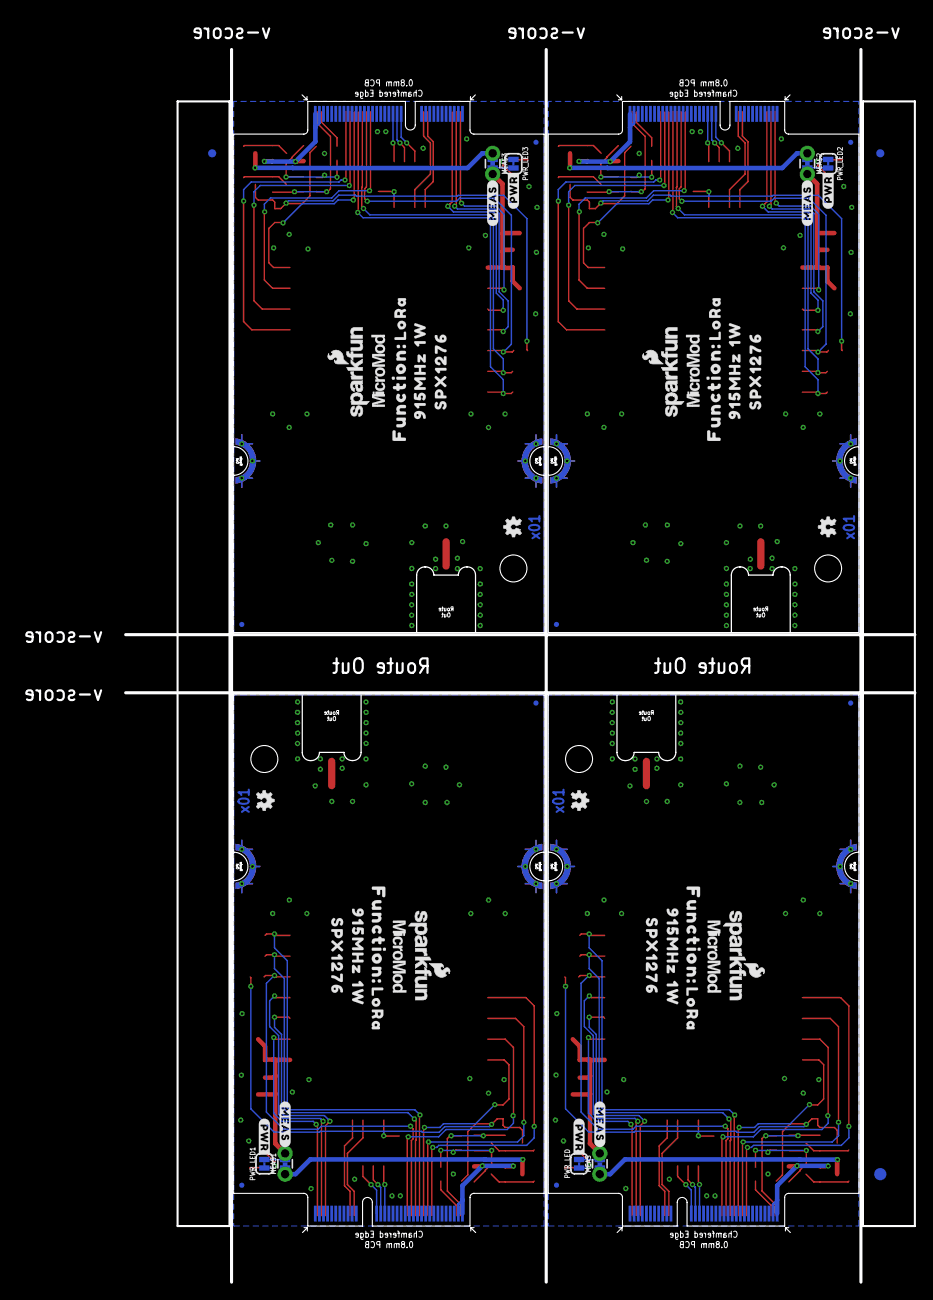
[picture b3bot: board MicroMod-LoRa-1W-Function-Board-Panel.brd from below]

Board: 2 copper layers, 96.6 x 150.8 mm, 202 parts (59 on the bottom side), 112 nets.

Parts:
C1, C3, C4, C6, C10, C11, C14, C17, C18, C20, C23, C24: 0.1uF; 0603
C2, C7, C15, C21: 10uF; EIA3216
C5, C12, C13, C19: 0.22uF; 0603
C8, C9, C16, C22: 68uF; EIA3528
D1, D2, D3, D5: RED; LED-0603
E1, E2, E3, E4: RP-SMA; SMA-EDGE-SMD
E$1, E$2, E$3, E$4: FIDUCIAL-1X2
E$5, E$6: FIDUCIAL-1.5X3
FD1, FD2, FD3, FD4, FD5, FD6, FD7, FD8, FD9, FD10, FD11, FD12, FD13, FD14, FD15, FD16: FIDUCIALUFIDUCIAL; FIDUCIAL-MICRO
H1, H2, H3, H4: STAND-OFF
J1, J2, J3, J11: MICROMOD_STANDARD; M.2-CARD-E-22_FUNCTION_STANDARD
LOGO1, LOGO2, LOGO4, LOGO6, LOGO7, LOGO9, LOGO10, LOGO12: SFE_LOGO_NAME_FLAME.1_INCH; SFE_LOGO_NAME_FLAME_.1
LOGO3, LOGO5, LOGO8, LOGO11: OSHW-LOGOMINI; OSHW-LOGO-MINI
MEAS, MEAS1, MEAS2, MEAS3: COMBO-JUMPER_2_NC_TRACE
PWR_LED, PWR_LED1, PWR_LED2, PWR_LED3: SMT-JUMPER_2_NC_TRACE_SILK
Q1, Q3, Q5, Q7, Q9, Q11, Q13, Q15: 20V/4.2A/52mΩ/1.4W; SOT23-3
Q2, Q4, Q6, Q8, Q10, Q12, Q14, Q16: 600mA/40V; SOT23-3
R1, R11, R15, R28: 1k; 0603
R2, R10, R24, R33: 470; 0603
R3, R4, R5, R6, R7, R8, R9, R12, R13, R14, R16, R17, R18, R19, R20, R21, R22, R23, R25, R26, R27, R29, R30, R31, R32, R34, R35, R36: 100k; 0603
U1, U3, U6, U8: EEPROM; SO08
U2, U4, U5, U7: E19-915M30S; E19-915MS1W
U$1, U$5, U$15, U$18, U$34, U$38, U$50, U$53: LORA0
U$2, U$13, U$21, U$30, U$32, U$41, U$48, U$56: 1W1
U$3, U$14, U$20, U$29, U$33, U$40, U$49, U$55: 915MHZ2
U$4, U$8, U$22, U$24, U$42, U$44, U$57, U$59: FUNCTION#0
U$6, U$16, U$19, U$27, U$35, U$39, U$51, U$54: SPX12763
U$7, U$17, U$36, U$52: PWR0
U$9, U$23, U$43, U$58: #PWR#0
U$10, U$11, U$25, U$26, U$37, U$45, U$46, U$63: MICROMOD_LOGO_.35
U$12, U$28, U$31, U$47: #MEAS#3

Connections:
3.3V: C3.1, C4.1, Q3.3, R16.2, R17.2, U1.8
3.3V1: C10.1, C11.1, Q1.3, R3.2, R5.2, U3.8
3.3V2: C17.1, C18.1, Q9.3, R20.2, R21.2, U6.8
3.3V3: C23.1, C24.1, Q13.3, R29.2, R30.2, U8.8
3.3V_IN: J11.73, Q3.2, Q4.2, R6.1
3.3V_IN1: J1.73, Q1.2, Q2.2, R13.1
3.3V_IN2: J2.73, Q9.2, Q10.2, R26.1
3.3V_IN3: J3.73, Q13.2, Q14.2, R35.1
5V: C1.1, C2.+, C8.A, C13.1, MEAS.2, MEAS.4, PWR_LED.2, U4.11
5V1: C5.1, C6.1, C7.+, C9.A, MEAS1.2, MEAS1.4, PWR_LED1.2, U2.11
5V2: C12.1, C14.1, C15.+, C16.A, MEAS2.2, MEAS2.4, PWR_LED2.2, U5.11
5V3: C19.1, C20.1, C21.+, C22.A, MEAS3.2, MEAS3.4, PWR_LED3.2, U7.11
A0: J11.36, U1.1
A1: J11.34, U1.2
A2: J11.32, U1.3
A3: J1.36, U3.1
A4: J1.32, U3.3
A5: J1.34, U3.2
A6: J2.36, U6.1
A7: J2.32, U6.3
A8: J2.34, U6.2
A9: J3.36, U8.1
A10: J3.32, U8.3
A11: J3.34, U8.2
GND: C1.2, C2.-, C3.2, C4.2, C8.C, C13.2, D5.C, E1.GND@0, E1.GND@1, J11.1, J11.33, J11.39, J11.45, J11.75, J11.GND1, J11.GND2, J11.GND3, J11.GND4, J11.GND5, J11.GND6, R4.1, R7.1, R18.1, R19.1, U1.4, U1.7, U4.1, U4.9, U4.10, U4.18, U4.20, U4.21, U4.22
GND1: C5.2, C6.2, C7.-, C9.C, C10.2, C11.2, D1.C, E2.GND@0, E2.GND@1, J1.1, J1.33, J1.39, J1.45, J1.75, J1.GND1, J1.GND2, J1.GND3, J1.GND4, J1.GND5, J1.GND6, R8.1, R9.1, R12.1, R14.1, U2.1, U2.9, U2.10, U2.18, U2.20, U2.21, U2.22, U3.4, U3.7
GND2: C12.2, C14.2, C15.-, C16.C, C17.2, C18.2, D2.C, E3.GND@0, E3.GND@1, J2.1, J2.33, J2.39, J2.45, J2.75, J2.GND1, J2.GND2, J2.GND3, J2.GND4, J2.GND5, J2.GND6, R22.1, R23.1, R25.1, R27.1, U5.1, U5.9, U5.10, U5.18, U5.20, U5.21, U5.22, U6.4, U6.7
GND3: C19.2, C20.2, C21.-, C22.C, C23.2, C24.2, D3.C, E4.GND@0, E4.GND@1, J3.1, J3.33, J3.39, J3.45, J3.75, J3.GND1, J3.GND2, J3.GND3, J3.GND4, J3.GND5, J3.GND6, R31.1, R32.1, R34.1, R36.1, U7.1, U7.9, U7.10, U7.18, U7.20, U7.21, U7.22, U8.4, U8.7
I2C_SCL: J11.21, U1.6
I2C_SCL1: J1.21, U3.6
I2C_SCL2: J2.21, U6.6
I2C_SCL3: J3.21, U8.6
I2C_SDA: J11.19, U1.5
I2C_SDA1: J1.19, U3.5
I2C_SDA2: J2.19, U6.5
I2C_SDA3: J3.19, U8.5
LORA_!CS!: J11.49, R17.1, U4.15
LORA_!CS!1: J1.49, R5.1, U2.15
LORA_!CS!2: J2.49, R21.1, U5.15
LORA_!CS!3: J3.49, R30.1, U7.15
LORA_!RST!: J11.55, R16.1, U4.8
LORA_!RST!1: J1.55, R3.1, U2.8
LORA_!RST!2: J2.55, R20.1, U5.8
LORA_!RST!3: J3.55, R29.1, U7.8
LORA_D0: J11.47, U4.7
LORA_D1: J11.57, U4.6
LORA_D2: J11.59, U4.5
LORA_D3: J1.47, U2.7
LORA_D4: J1.57, U2.6
LORA_D5: J1.59, U2.5
LORA_D6: J2.47, U5.7
LORA_D7: J2.57, U5.6
LORA_D8: J2.59, U5.5
LORA_D9: J3.47, U7.7
LORA_D10: J3.57, U7.6
LORA_D11: J3.59, U7.5
LORA_RXEN: J11.53, R18.2, U4.17
LORA_RXEN1: J1.53, R8.2, U2.17
LORA_RXEN2: J2.53, R22.2, U5.17
LORA_RXEN3: J3.53, R31.2, U7.17
LORA_TXEN: J11.51, R19.2, U4.16
LORA_TXEN1: J1.51, R9.2, U2.16
LORA_TXEN2: J2.51, R23.2, U5.16
LORA_TXEN3: J3.51, R32.2, U7.16
unnamed: E1.SIG, U4.19
unnamed: PWR_LED1.1, R1.2
unnamed: D1.A, R1.1
unnamed: J11.71, R2.2
unnamed: D5.A, R11.1
unnamed: PWR_LED.1, R11.2
unnamed: E2.SIG, U2.19
unnamed: J1.71, R10.2
unnamed: Q3.1, Q4.3, R4.2
unnamed: Q1.1, Q2.3, R12.2
unnamed: Q5.1, Q6.3, R7.2
unnamed: Q7.1, Q8.3, R14.2
unnamed: PWR_LED2.1, R15.2
unnamed: D2.A, R15.1
unnamed: E3.SIG, U5.19
unnamed: J2.71, R24.2
unnamed: Q9.1, Q10.3, R25.2
unnamed: Q11.1, Q12.3, R27.2
unnamed: PWR_LED3.1, R28.2
unnamed: D3.A, R28.1
unnamed: E4.SIG, U7.19
unnamed: J3.71, R33.2
unnamed: Q13.1, Q14.3, R34.2
unnamed: Q15.1, Q16.3, R36.2
PWR_EN: Q4.1, Q6.1, R2.1, R6.2
PWR_EN1: Q2.1, Q8.1, R10.1, R13.2
PWR_EN2: Q10.1, Q12.1, R24.1, R26.2
PWR_EN3: Q14.1, Q16.1, R33.1, R35.2
SPI_CIPO: J11.7, U4.13
SPI_CIPO1: J1.7, U2.13
SPI_CIPO2: J2.7, U5.13
SPI_CIPO3: J3.7, U7.13
SPI_COPI: J11.5, U4.14
SPI_COPI1: J1.5, U2.14
SPI_COPI2: J2.5, U5.14
SPI_COPI3: J3.5, U7.14
SPI_SCK: J11.3, U4.12
SPI_SCK1: J1.3, U2.12
SPI_SCK2: J2.3, U5.12
SPI_SCK3: J3.3, U7.12
VCC: MEAS.1, MEAS.3, Q5.3
VCC1: MEAS1.1, MEAS1.3, Q7.3
VCC2: MEAS2.1, MEAS2.3, Q11.3
VCC3: MEAS3.1, MEAS3.3, Q15.3
VCC_IN: J11.72, J11.74, Q5.2, Q6.2
VCC_IN1: J1.72, J1.74, Q7.2, Q8.2
VCC_IN2: J2.72, J2.74, Q11.2, Q12.2
VCC_IN3: J3.72, J3.74, Q15.2, Q16.2

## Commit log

2021-09-14 Update PoE module to DP990X.
2021-09-20 Add x01 panel files
2021-09-21 Update PROD_IDs
2021-09-21 Remove old files
2021-09-21 Change load resistor to 1206.
2021-10-27 Connect PWR LED to 3.3V rail. Add POE LED. Add pin 1 indicator to PoE module. Add hot caution.
2021-10-29 Add PoE datasheet and firmware test.
2021-11-05 Add ESD to TX/RX, landmarks to PoE module, additional GND thermals.
2021-11-08 Add dimensions
2022-02-14 Create README.md
    Adding README.md file
2022-03-02 Add -W5500 to file names
2022-03-02 Mark ESD IC as DNP
2022-03-10 Update README.md
    Updating README with new photo link.
